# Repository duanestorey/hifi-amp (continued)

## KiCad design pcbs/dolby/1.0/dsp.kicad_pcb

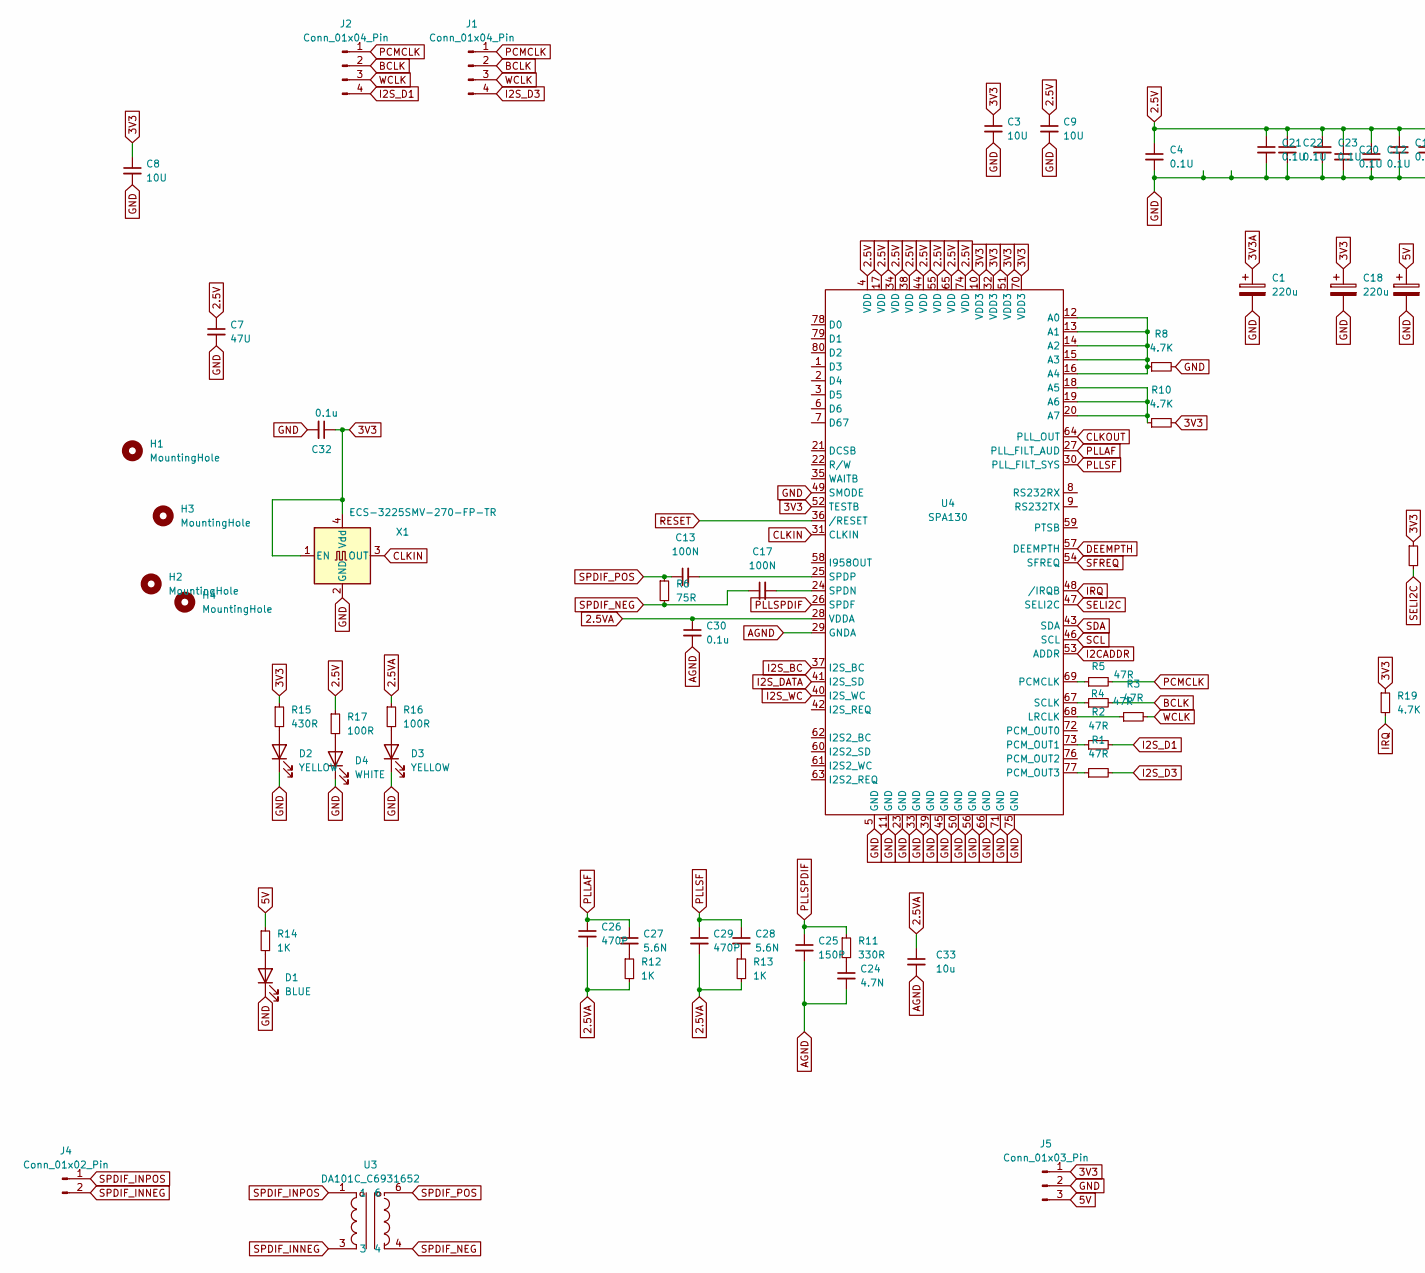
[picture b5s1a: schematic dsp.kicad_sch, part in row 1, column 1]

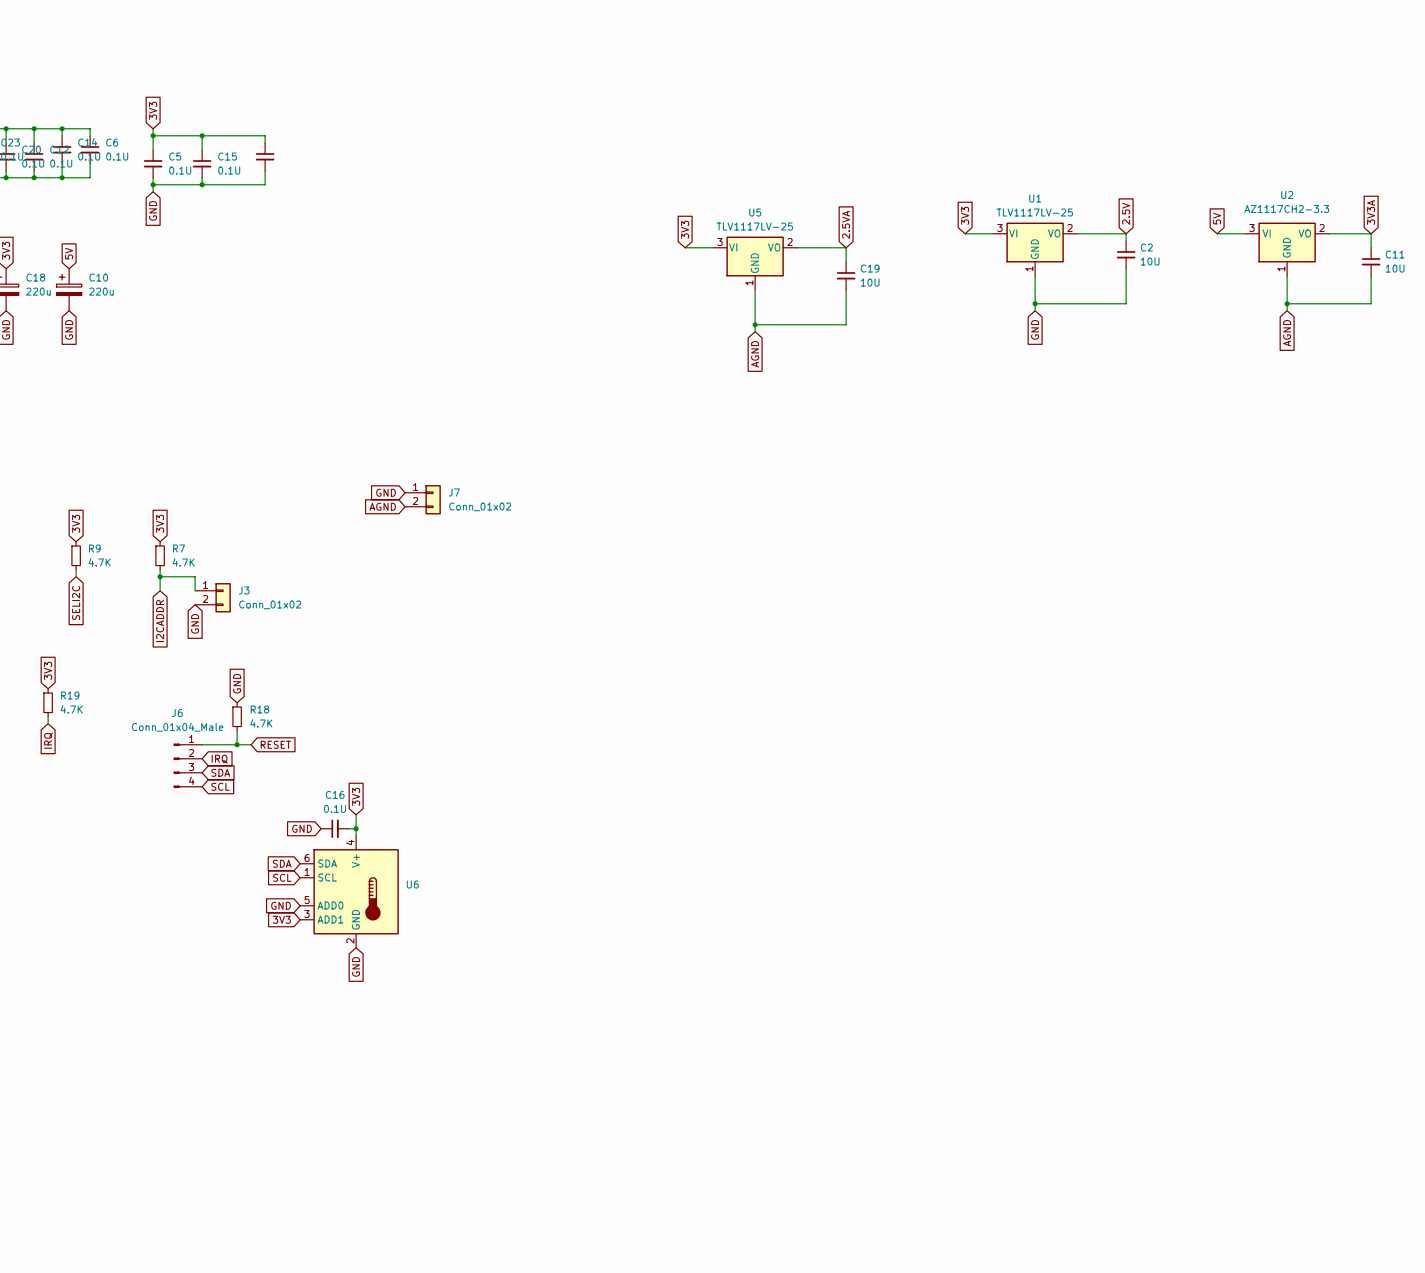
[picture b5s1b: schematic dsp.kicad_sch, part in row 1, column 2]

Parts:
C1, C10, C18: 220u; CP_Radial_D6.3mm_P2.50mm
C2, C3, C8, C9, C11, C19: 10U; C_1206_3216Metric_Pad1.33x1.80mm_HandSolder
C4, C5, C6, C12, C14, C15, C16, C20, C21, C22, C23, C31: 0.1U; C_0805_2012Metric_Pad1.18x1.45mm_HandSolder
C7: 47U; C_1206_3216Metric_Pad1.33x1.80mm_HandSolder
C13, C17: 100N; C_0805_2012Metric_Pad1.18x1.45mm_HandSolder
C24: 4.7N; C_0805_2012Metric_Pad1.18x1.45mm_HandSolder
C25: 150P; C_0805_2012Metric_Pad1.18x1.45mm_HandSolder
C26, C29: 470P; C_0805_2012Metric_Pad1.18x1.45mm_HandSolder
C27, C28: 5.6N; C_0805_2012Metric_Pad1.18x1.45mm_HandSolder
C30, C32: 0.1u; C_0805_2012Metric_Pad1.18x1.45mm_HandSolder
C33: 10u; C_1206_3216Metric_Pad1.33x1.80mm_HandSolder
D1: BLUE; LED_0805_2012Metric_Pad1.15x1.40mm_HandSolder
D2, D3: YELLOW; LED_0805_2012Metric_Pad1.15x1.40mm_HandSolder
D4: WHITE; LED_0805_2012Metric_Pad1.15x1.40mm_HandSolder
H1, H2, H3, H4: MountingHole; MountingHole_3.2mm_M3
J1, J2: Conn_01x04_Pin; JST_PH_B4B-PH-K_1x04_P2.00mm_Vertical
J3, J7: Conn_01x02; PinHeader_1x02_P2.54mm_Vertical
J4: Conn_01x02_Pin; JST_XH_B2B-XH-A_1x02_P2.50mm_Vertical
J5: Conn_01x03_Pin; JST_PH_B3B-PH-K_1x03_P2.00mm_Vertical
J6: Conn_01x04_Male; JST_PH_B4B-PH-K_1x04_P2.00mm_Vertical
R1, R2, R3, R4, R5: 47R; R_0805_2012Metric_Pad1.20x1.40mm_HandSolder
R6: 75R; R_0603_1608Metric_Pad0.98x0.95mm_HandSolder
R7, R8, R9, R10, R18, R19: 4.7K; R_0603_1608Metric_Pad0.98x0.95mm_HandSolder
R11: 330R; R_0603_1608Metric_Pad0.98x0.95mm_HandSolder
R12, R13, R14: 1K; R_0603_1608Metric_Pad0.98x0.95mm_HandSolder
R15: 430R; R_0603_1608Metric_Pad0.98x0.95mm_HandSolder
R16, R17: 100R; R_0603_1608Metric_Pad0.98x0.95mm_HandSolder
U1, U5: TLV1117LV-25; SOT-223-3_TabPin2
U2: AZ1117CH2-3.3; SOT-223-3_TabPin2
U3: DA101C_C6931652; XFMR-TH_4P-L9.5-W9.0-P5.08-LS10.2_C9900096976; LCSC Part C6931652
U4: SPA130; LQFP-80_14x14mm_P0.65mm
U6: TMP100; SOT-23-6
X1: ECS-3225SMV-270-FP-TR; Oscillator_SMD_EuroQuartz_XO32-4Pin_3.2x2.5mm_HandSoldering

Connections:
2.5V: C2.1, C4.1, C6.1, C7.1, C9.1, C12.1, C14.1, C20.1, C21.1, C22.1, C23.1, R17.1, U1.2 (VO), U4.4 (VDD), U4.17 (VDD), U4.34 (VDD), U4.38 (VDD), U4.44 (VDD), U4.55 (VDD), U4.65 (VDD), U4.74 (VDD)
2.5VA: C19.1, C26.2, C29.2, C30.1, C33.1, R12.2, R13.2, R16.1, U4.28 (VDDA), U5.2 (VO)
3V3: C3.1, C5.1, C8.1, C15.1, C16.2, C18.1, C31.1, C32.1, J5.1, R7.1, R9.1, R10.2, R15.1, R19.1, U1.3 (VI), U4.10 (VDD3), U4.32 (VDD3), U4.51 (VDD3), U4.52 (TESTB), U4.70 (VDD3), U5.3 (VI), U6.3 (ADD1), U6.4 (V+), X1.1 (EN), X1.4 (Vdd)
3V3A: C1.1, C11.1, U2.2 (VO)
5V: C10.1, J5.3, R14.1, U2.3 (VI)
AGND: C11.2, C19.2, C24.2, C25.2, C30.2, C33.2, J7.2, U2.1 (GND), U4.29 (GNDA), U5.1 (GND)
BCLK: J1.2, J2.2, R4.2
CLKIN: U4.31 (CLKIN), X1.3 (OUT)
CLKOUT: U4.64 (PLL_OUT)
DEEMPTH: U4.57 (DEEMPTH)
GND: C1.2, C2.2, C3.2, C4.2, C5.2, C6.2, C7.2, C8.2, C9.2, C10.2, C12.2, C14.2, C15.2, C16.1, C18.2, C20.2, C21.2, C22.2, C23.2, C31.2, C32.2, D1.1 (K), D2.1 (K), D3.1 (K), D4.1 (K), J3.2, J5.2, J7.1, R8.2, R18.1, U1.1 (GND), U4.5 (GND), U4.11 (GND), U4.23 (GND), U4.33 (GND), U4.39 (GND), U4.45 (GND), U4.49 (SMODE), U4.50 (GND), U4.56 (GND), U4.66 (GND), U4.71 (GND), U4.75 (GND), U6.2 (GND), U6.5 (ADD0), X1.2 (GND)
I2CADDR: J3.1, R7.2, U4.53 (ADDR)
I2S_BC: U4.37 (I2S_BC)
I2S_D1: J2.4, R2.2
I2S_D3: J1.4, R1.2
I2S_DATA: U4.41 (I2S_SD)
I2S_WC: U4.40 (I2S_WC)
IRQ: J6.2, R19.2, U4.48 (/IRQB)
unnamed: C24.1, R11.2
unnamed: C27.2, R12.1
unnamed: C28.2, R13.1
unnamed: D1.2 (A), R14.2
unnamed: D2.2 (A), R15.2
unnamed: D3.2 (A), R16.2
unnamed: D4.2 (A), R17.2
unnamed: R8.1, U4.12 (A0), U4.13 (A1), U4.14 (A2), U4.15 (A3), U4.16 (A4)
unnamed: R10.1, U4.18 (A5), U4.19 (A6), U4.20 (A7)
unnamed: R3.1, U4.68 (LRCLK)
unnamed: R5.1, U4.69 (PCMCLK)
unnamed: R2.1, U4.73 (PCM_OUT1)
unnamed: R1.1, U4.77 (PCM_OUT3)
unnamed: R4.1, U4.67 (SCLK)
unnamed: C17.2, U4.24 (SPDN)
unnamed: C13.2, U4.25 (SPDP)
PCMCLK: J1.1, J2.1, R5.2
PLLAF: C26.1, C27.1, U4.27 (PLL_FILT_AUD)
PLLSF: C28.1, C29.1, U4.30 (PLL_FILT_SYS)
PLLSPDIF: C25.1, R11.1, U4.26 (SPDF)
RESET: J6.1, R18.2, U4.36 (/RESET)
SCL: J6.4, U4.46 (SCL), U6.1 (SCL)
SDA: J6.3, U4.43 (SDA), U6.6 (SDA)
SELI2C: R9.2, U4.47 (SELI2C)
SFREQ: U4.54 (SFREQ)
SPDIF_INNEG: J4.2, U3.3
SPDIF_INPOS: J4.1, U3.1
SPDIF_NEG: C17.1, R6.2, U3.4
SPDIF_POS: C13.1, R6.1, U3.6
WCLK: J1.3, J2.3, R3.2

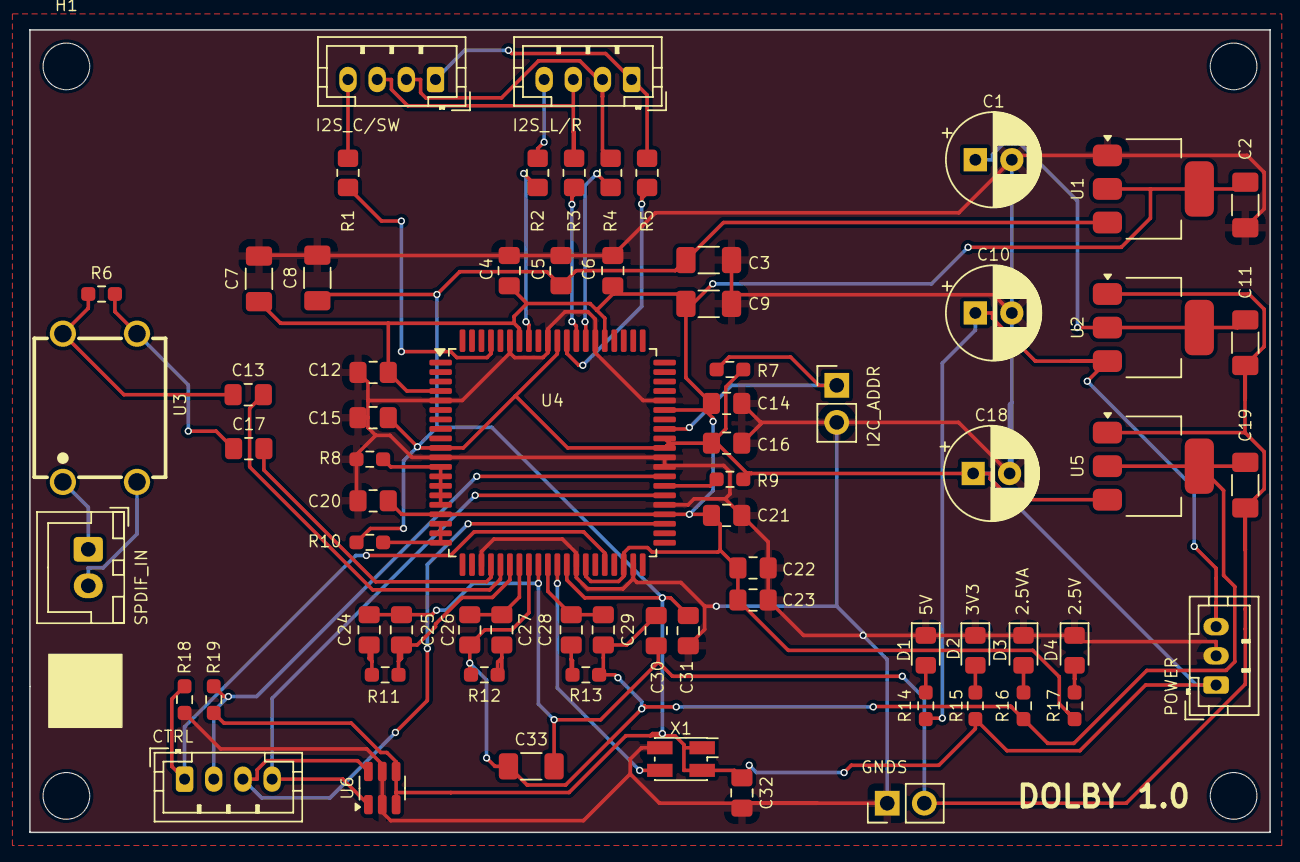
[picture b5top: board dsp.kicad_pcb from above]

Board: 2 copper layers, 85.0 x 55.0 mm, 74 parts (0 on the bottom side), 42 nets.

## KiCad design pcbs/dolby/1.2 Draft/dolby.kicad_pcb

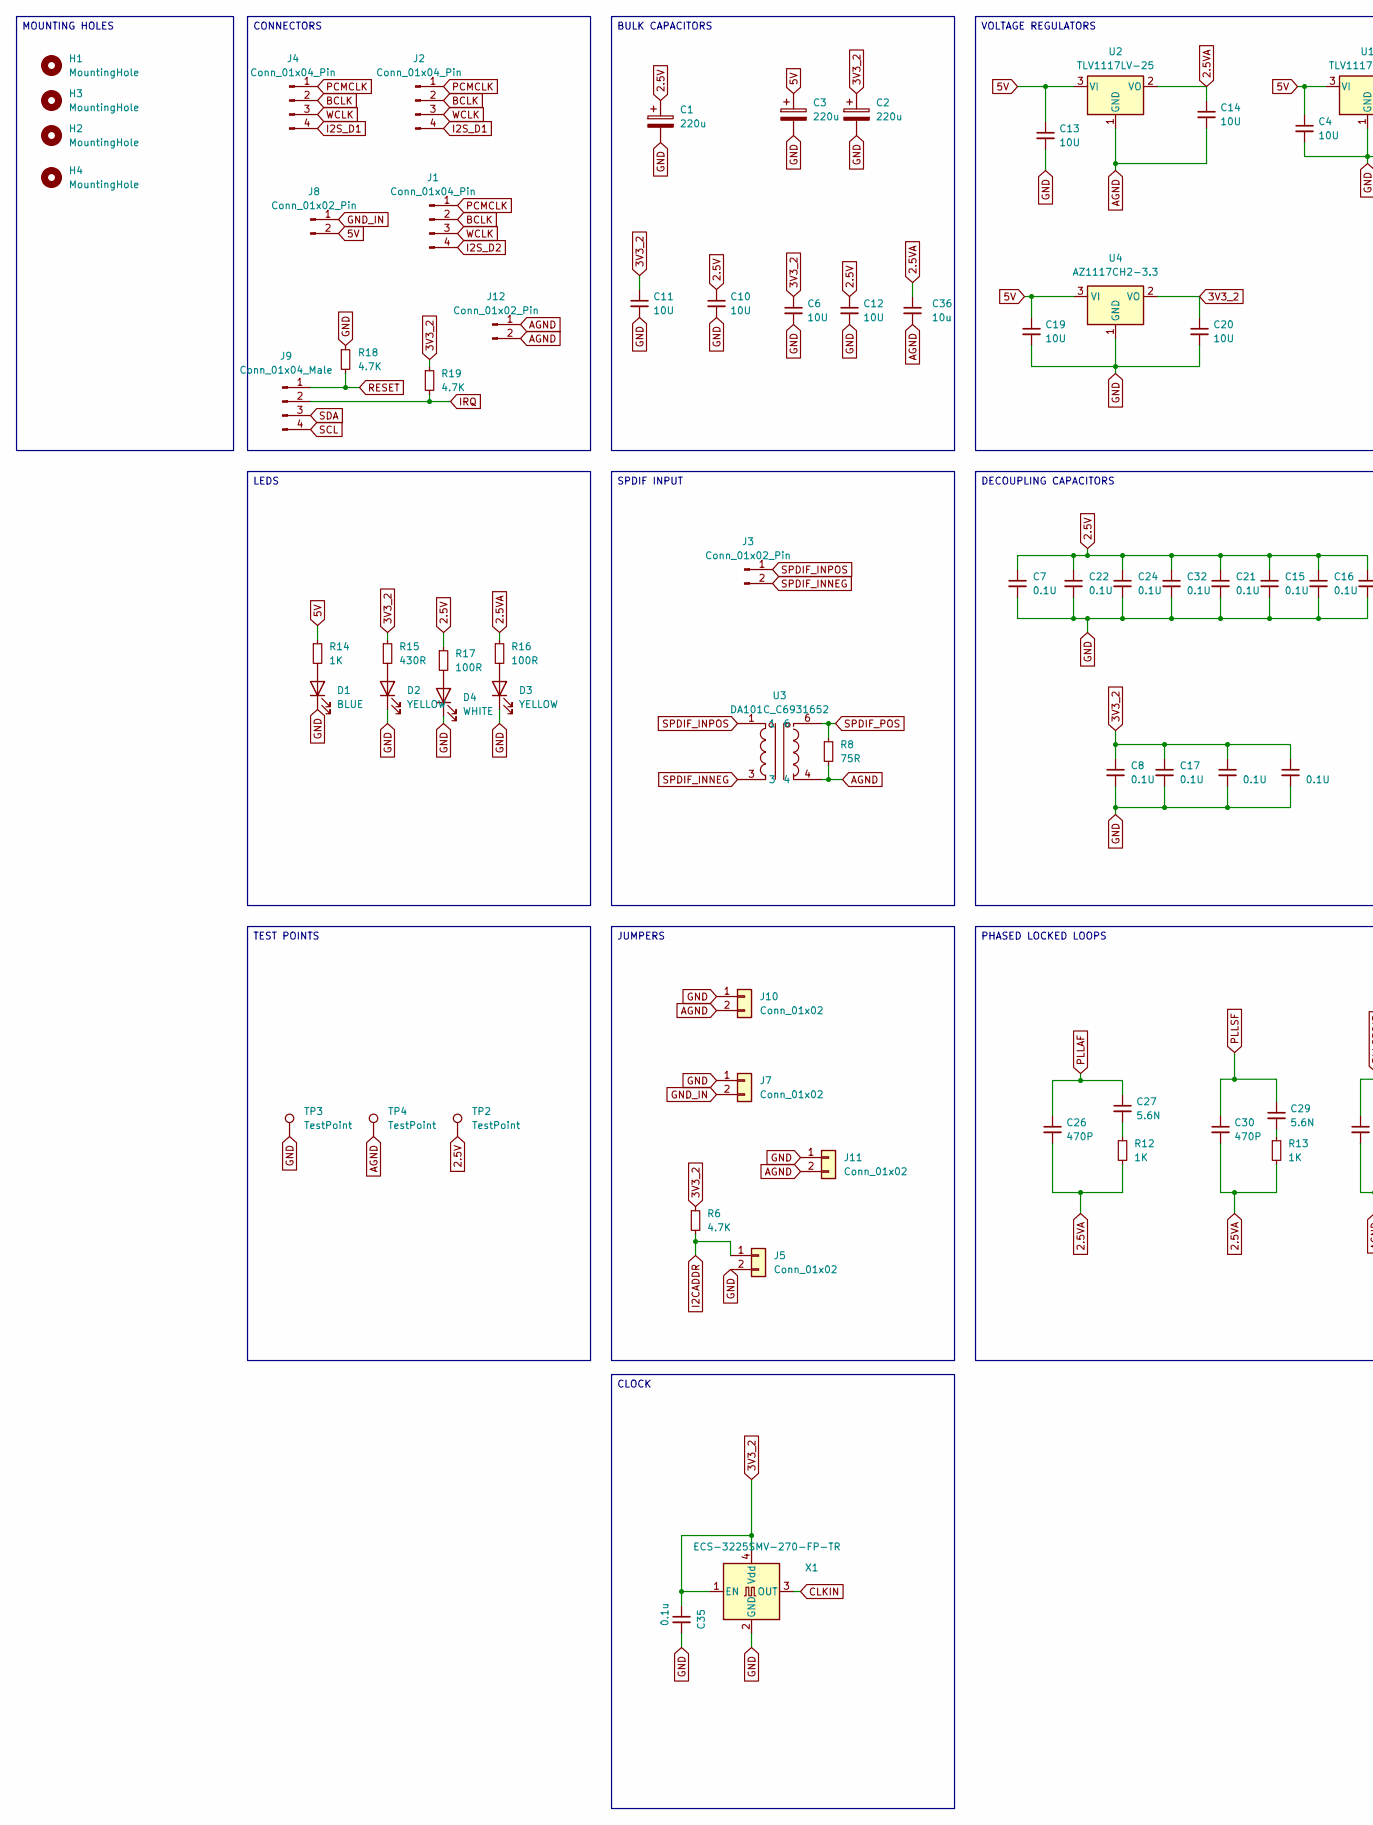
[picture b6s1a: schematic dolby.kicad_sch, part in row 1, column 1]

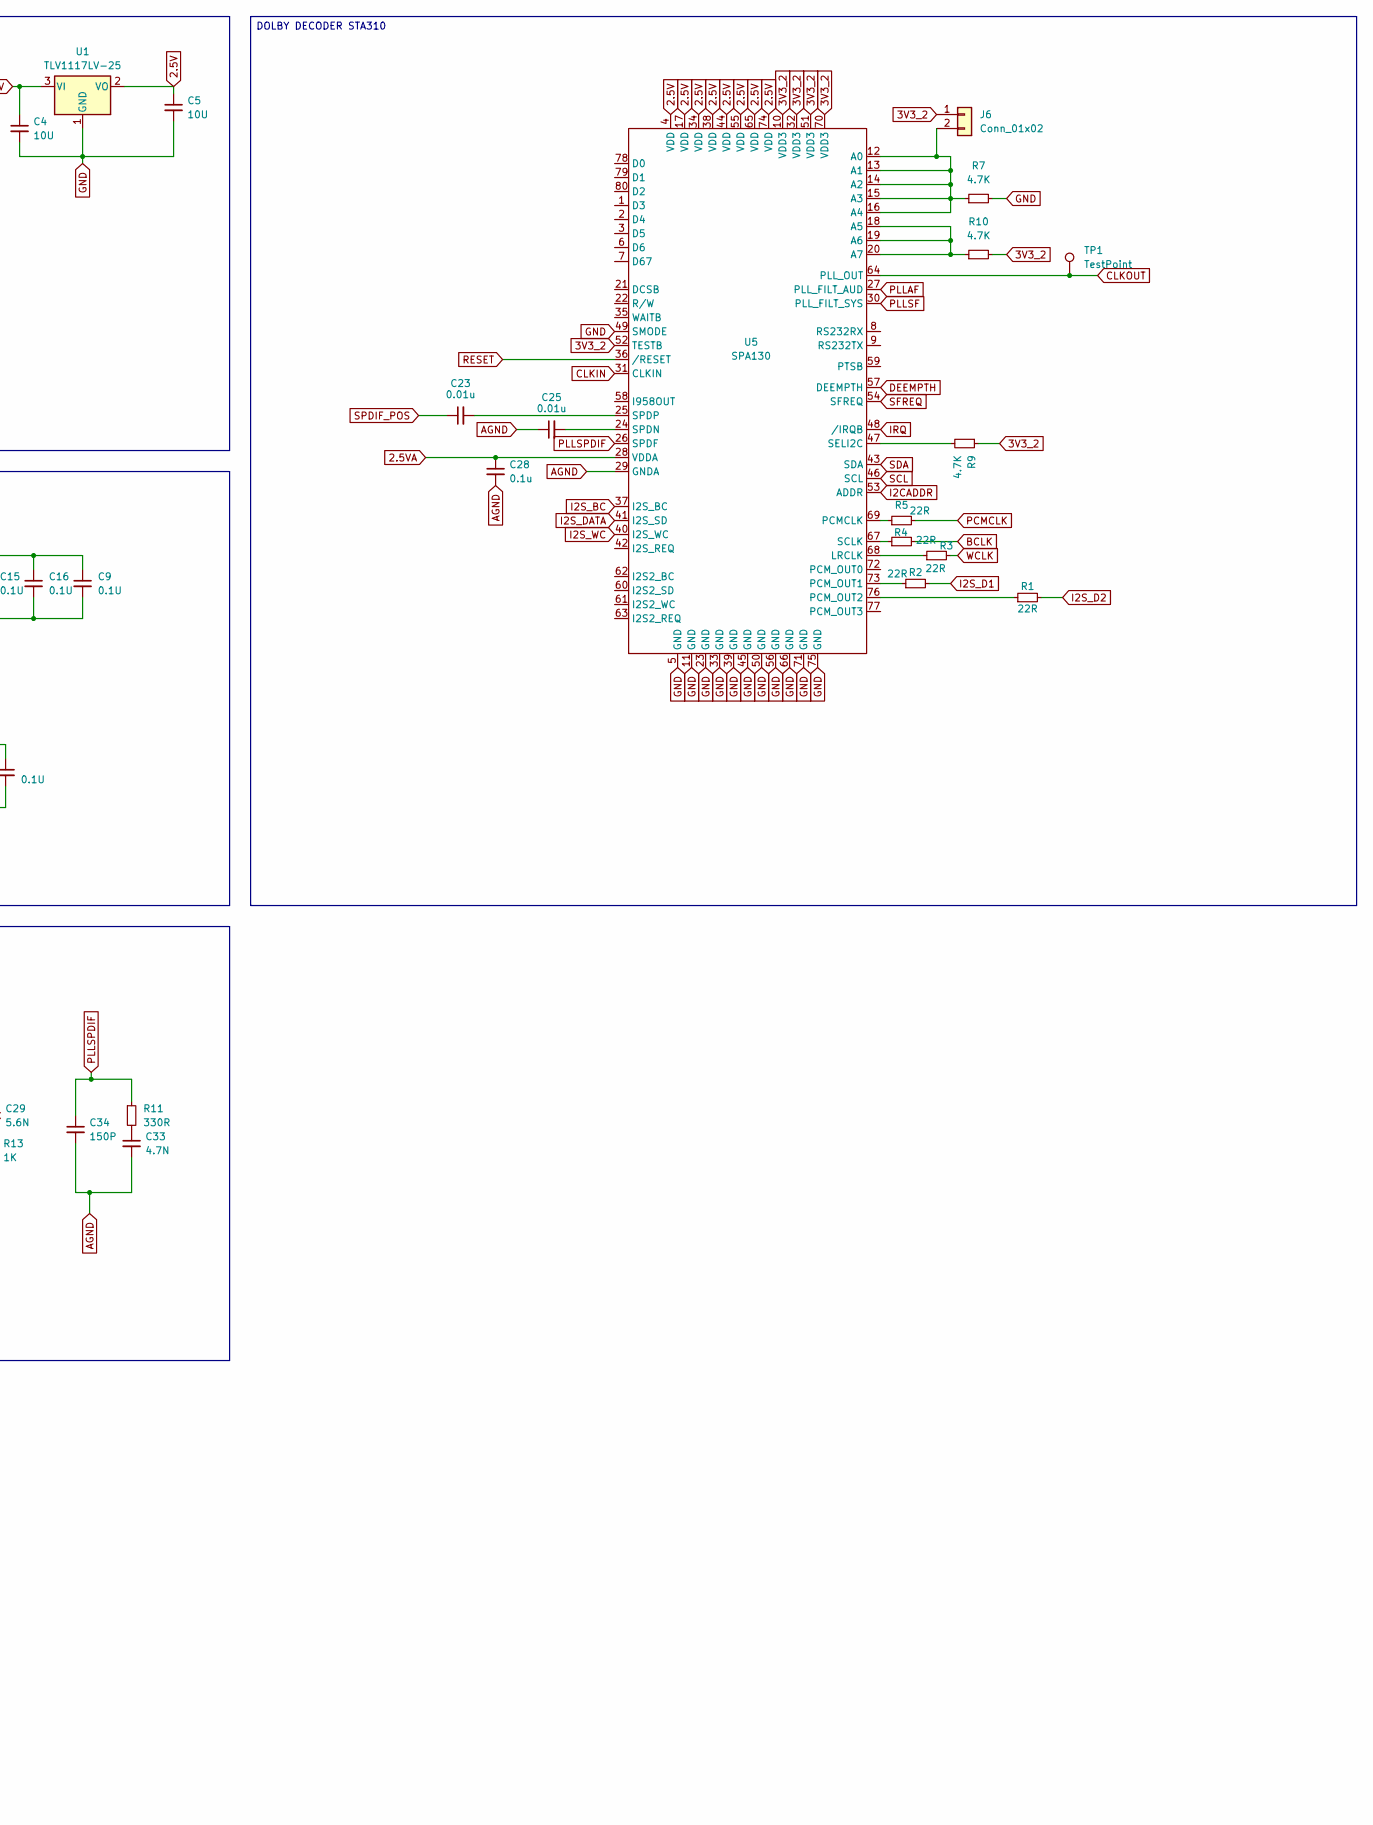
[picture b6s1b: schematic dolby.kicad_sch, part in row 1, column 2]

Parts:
C1, C2, C3: 220u; CP_Radial_D6.3mm_P2.50mm
C4, C5, C6, C10, C11, C12, C13, C14, C19, C20: 10U; C_1206_3216Metric_Pad1.33x1.80mm_HandSolder
C7, C8, C9, C15, C16, C17, C18, C21, C22, C24, C31, C32: 0.1U; C_0805_2012Metric_Pad1.18x1.45mm_HandSolder
C23, C25: 0.01u; C_0805_2012Metric_Pad1.18x1.45mm_HandSolder
C26, C30: 470P; C_0805_2012Metric_Pad1.18x1.45mm_HandSolder
C27, C29: 5.6N; C_0805_2012Metric_Pad1.18x1.45mm_HandSolder
C28, C35: 0.1u; C_0805_2012Metric_Pad1.18x1.45mm_HandSolder
C33: 4.7N; C_0805_2012Metric_Pad1.18x1.45mm_HandSolder
C34: 150P; C_0805_2012Metric_Pad1.18x1.45mm_HandSolder
C36: 10u; C_1206_3216Metric_Pad1.33x1.80mm_HandSolder
D1: BLUE; LED_0805_2012Metric_Pad1.15x1.40mm_HandSolder
D2, D3: YELLOW; LED_0805_2012Metric_Pad1.15x1.40mm_HandSolder
D4: WHITE; LED_0805_2012Metric_Pad1.15x1.40mm_HandSolder
H1, H2, H3, H4: MountingHole; MountingHole_3.2mm_M3_DIN965_Pad_TopBottom
J1, J2: Conn_01x04_Pin; JST_PH_B4B-PH-K_1x04_P2.00mm_Vertical
J3: Conn_01x02_Pin; JST_XH_B2B-XH-A_1x02_P2.50mm_Vertical
J4: Conn_01x04_Pin; PinHeader_1x04_P2.54mm_Vertical
J5, J6, J7, J10, J11: Conn_01x02; PinHeader_1x02_P2.54mm_Vertical
J8, J12: Conn_01x02_Pin; JST_PH_B2B-PH-K_1x02_P2.00mm_Vertical
J9: Conn_01x04_Male; JST_PH_B4B-PH-K_1x04_P2.00mm_Vertical
R1, R2, R3, R4, R5: 22R; R_0805_2012Metric_Pad1.20x1.40mm_HandSolder
R6, R7, R9, R10, R18, R19: 4.7K; R_0603_1608Metric_Pad0.98x0.95mm_HandSolder
R8: 75R; R_0805_2012Metric_Pad1.20x1.40mm_HandSolder
R11: 330R; R_0603_1608Metric_Pad0.98x0.95mm_HandSolder
R12, R13, R14: 1K; R_0603_1608Metric_Pad0.98x0.95mm_HandSolder
R15: 430R; R_0603_1608Metric_Pad0.98x0.95mm_HandSolder
R16, R17: 100R; R_0603_1608Metric_Pad0.98x0.95mm_HandSolder
TP1, TP2, TP3, TP4: TestPoint; TestPoint_THTPad_D2.0mm_Drill1.0mm
U1, U2: TLV1117LV-25; SOT-223-3_TabPin2
U3: DA101C_C6931652; XFMR-TH_4P-L9.5-W9.0-P5.08-LS10.2_C9900096976; LCSC Part C6931652
U4: AZ1117CH2-3.3; SOT-223-3_TabPin2
U5: SPA130; LQFP-80_14x14mm_P0.65mm
X1: ECS-3225SMV-270-FP-TR; Oscillator_SMD_EuroQuartz_XO32-4Pin_3.2x2.5mm_HandSoldering

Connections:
2.5V: C1.1, C5.1, C7.1, C9.1, C10.1, C12.1, C15.1, C16.1, C21.1, C22.1, C24.1, C32.1, R17.1, TP2.1, U1.2 (VO), U5.4 (VDD), U5.17 (VDD), U5.34 (VDD), U5.38 (VDD), U5.44 (VDD), U5.55 (VDD), U5.65 (VDD), U5.74 (VDD)
2.5VA: C14.1, C26.2, C28.1, C30.2, C36.1, R12.2, R13.2, R16.1, U2.2 (VO), U5.28 (VDDA)
3V3_2: C2.1, C6.1, C8.1, C11.1, C17.1, C18.1, C20.1, C31.1, C35.1, J6.1, R6.1, R9.1, R10.2, R15.1, R19.1, U4.2 (VO), U5.10 (VDD3), U5.32 (VDD3), U5.51 (VDD3), U5.52 (TESTB), U5.70 (VDD3), X1.1 (EN), X1.4 (Vdd)
5V: C3.1, C4.1, C13.1, C19.1, J8.2, R14.1, U1.3 (VI), U2.3 (VI), U4.3 (VI)
AGND: C14.2, C25.1, C28.2, C33.2, C34.2, C36.2, J10.2, J11.2, J12.1, J12.2, R8.2, TP4.1, U2.1 (GND), U3.4, U5.29 (GNDA)
BCLK: J1.2, J2.2, J4.2, R4.2
CLKIN: U5.31 (CLKIN), X1.3 (OUT)
CLKOUT: TP1.1, U5.64 (PLL_OUT)
DEEMPTH: U5.57 (DEEMPTH)
GND: C1.2, C2.2, C3.2, C4.2, C5.2, C6.2, C7.2, C8.2, C9.2, C10.2, C11.2, C12.2, C13.2, C15.2, C16.2, C17.2, C18.2, C19.2, C20.2, C21.2, C22.2, C24.2, C31.2, C32.2, C35.2, D1.1 (K), D2.1 (K), D3.1 (K), D4.1 (K), J5.2, J7.1, J10.1, J11.1, R7.2, R18.1, TP3.1, U1.1 (GND), U4.1 (GND), U5.5 (GND), U5.11 (GND), U5.23 (GND), U5.33 (GND), U5.39 (GND), U5.45 (GND), U5.49 (SMODE), U5.50 (GND), U5.56 (GND), U5.66 (GND), U5.71 (GND), U5.75 (GND), X1.2 (GND)
GND_IN: J7.2, J8.1
I2CADDR: J5.1, R6.2, U5.53 (ADDR)
I2S_BC: U5.37 (I2S_BC)
I2S_D1: J2.4, J4.4, R2.2
I2S_D2: J1.4, R1.2
I2S_DATA: U5.41 (I2S_SD)
I2S_WC: U5.40 (I2S_WC)
IRQ: J9.2, R19.2, U5.48 (/IRQB)
unnamed: C27.2, R12.1
unnamed: C29.2, R13.1
unnamed: C33.1, R11.2
unnamed: D1.2 (A), R14.2
unnamed: D2.2 (A), R15.2
unnamed: D3.2 (A), R16.2
unnamed: D4.2 (A), R17.2
unnamed: J6.2, R7.1, U5.12 (A0), U5.13 (A1), U5.14 (A2), U5.15 (A3), U5.16 (A4)
unnamed: R10.1, U5.18 (A5), U5.19 (A6), U5.20 (A7)
unnamed: R3.1, U5.68 (LRCLK)
unnamed: R5.1, U5.69 (PCMCLK)
unnamed: R2.1, U5.73 (PCM_OUT1)
unnamed: R1.1, U5.76 (PCM_OUT2)
unnamed: R4.1, U5.67 (SCLK)
unnamed: R9.2, U5.47 (SELI2C)
unnamed: C25.2, U5.24 (SPDN)
unnamed: C23.2, U5.25 (SPDP)
PCMCLK: J1.1, J2.1, J4.1, R5.2
PLLAF: C26.1, C27.1, U5.27 (PLL_FILT_AUD)
PLLSF: C29.1, C30.1, U5.30 (PLL_FILT_SYS)
PLLSPDIF: C34.1, R11.1, U5.26 (SPDF)
RESET: J9.1, R18.2, U5.36 (/RESET)
SCL: J9.4, U5.46 (SCL)
SDA: J9.3, U5.43 (SDA)
SFREQ: U5.54 (SFREQ)
SPDIF_INNEG: J3.2, U3.3
SPDIF_INPOS: J3.1, U3.1
SPDIF_POS: C23.1, R8.1, U3.6
WCLK: J1.3, J2.3, J4.3, R3.2

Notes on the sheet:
CLOCK
CONNECTORS
JUMPERS
TEST POINTS
VOLTAGE REGULATORS
DOLBY DECODER STA310
LEDS
BULK CAPACITORS
PHASED LOCKED LOOPS
SPDIF INPUT
MOUNTING HOLES
DECOUPLING CAPACITORS

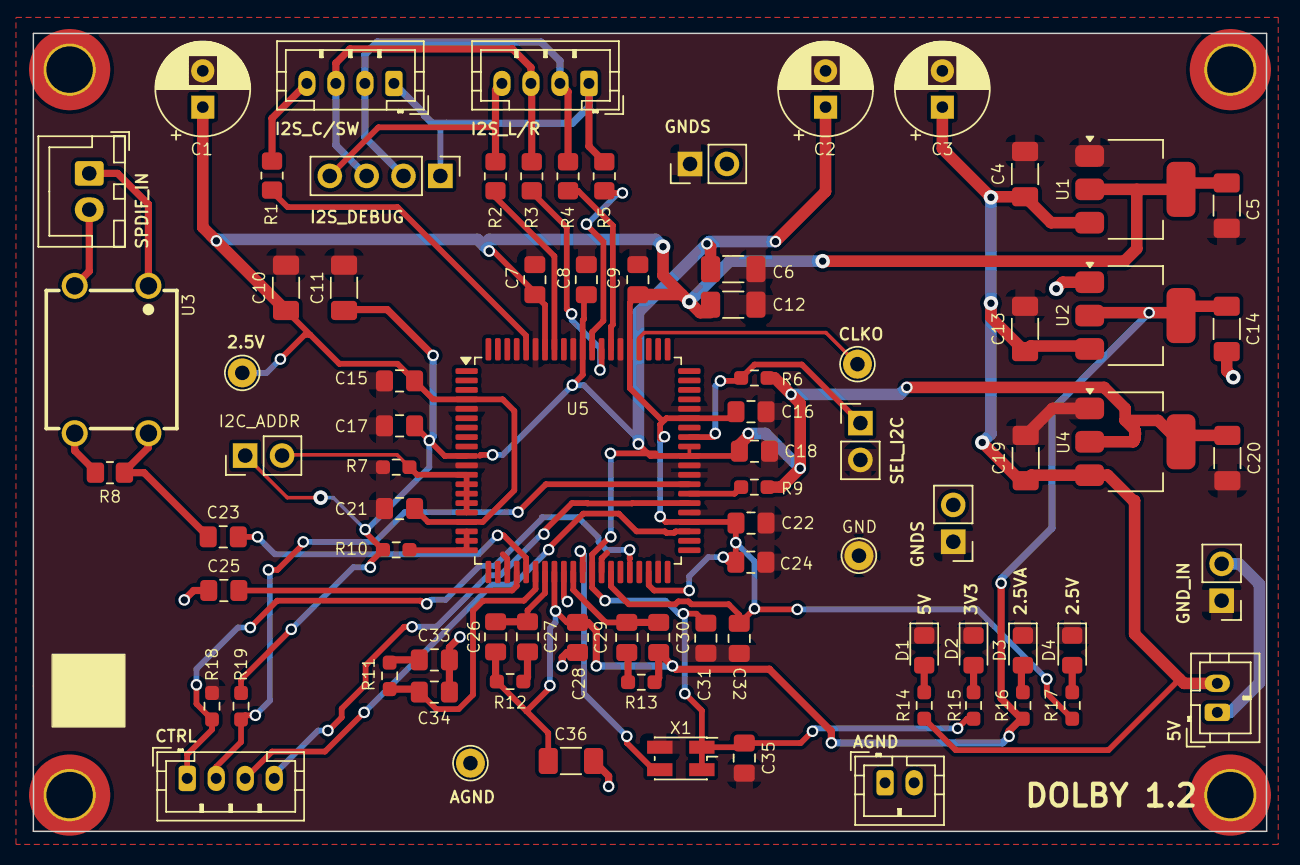
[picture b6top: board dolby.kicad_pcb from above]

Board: 2 copper layers, 85.0 x 55.0 mm, 85 parts (0 on the bottom side), 42 nets.
